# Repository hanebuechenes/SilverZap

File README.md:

## 📜 Lizenzierung / License

Dieses Projekt ist unter dualen Open-Source-Lizenzen veröffentlicht:

* **Hardware & Design (KiCad, Gerber, 3D-STL/STEP):**  
  Lizenziert unter [Creative Commons Attribution 4.0 International (CC BY 4.0)](LICENSE-HARDWARE.txt).  

* **Software & Firmware (C++ Source Code):**  
  Lizenziert unter der [GNU General Public License v3.0 (GPLv3)](LICENSE).

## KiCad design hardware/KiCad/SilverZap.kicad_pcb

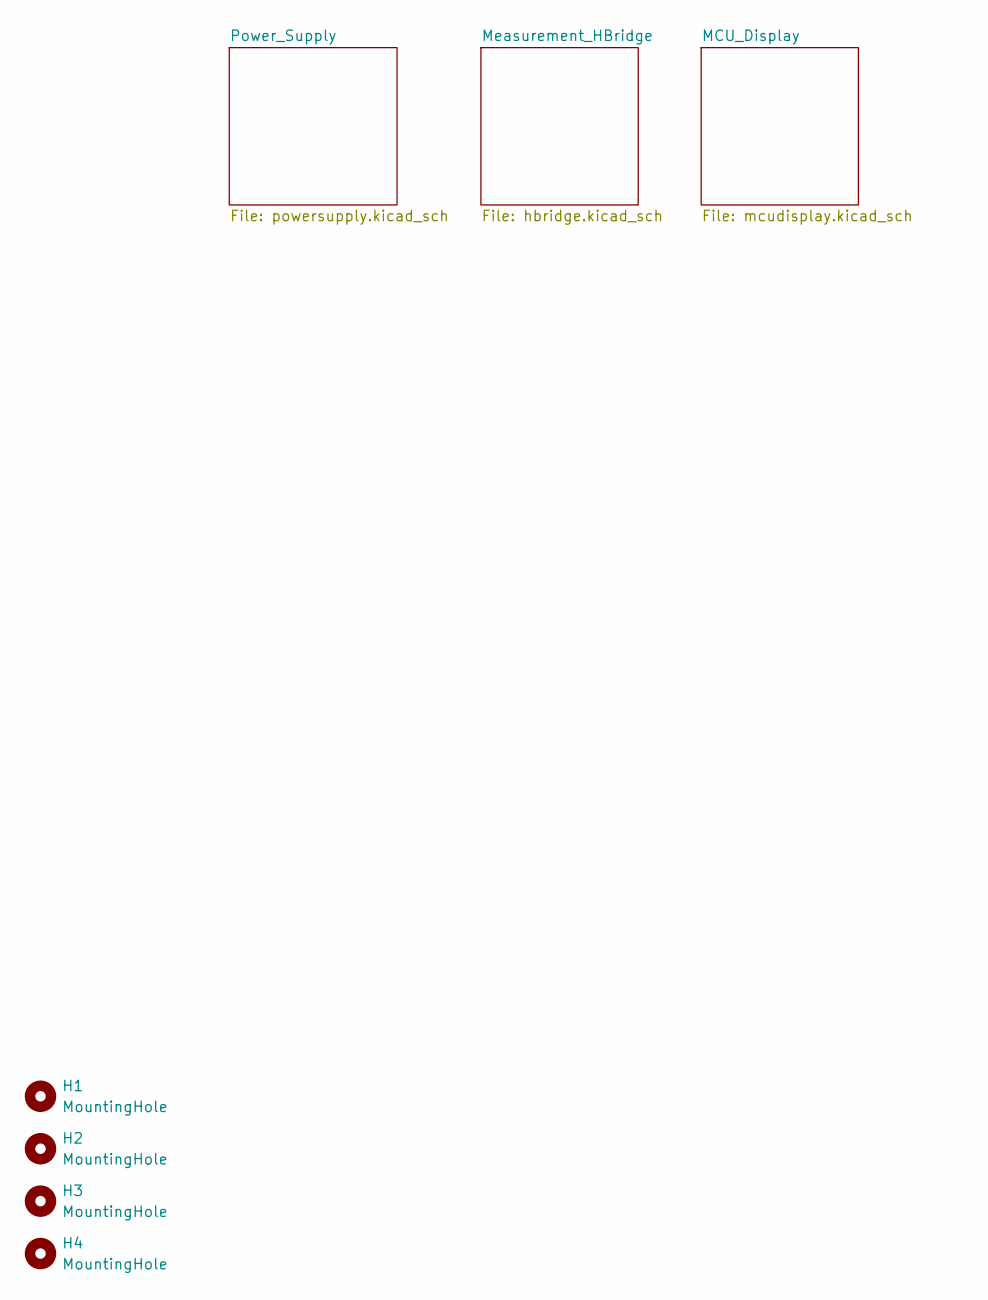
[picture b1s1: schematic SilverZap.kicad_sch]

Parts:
H1, H2, H3, H4: MountingHole; MountingHole_3.2mm_M3

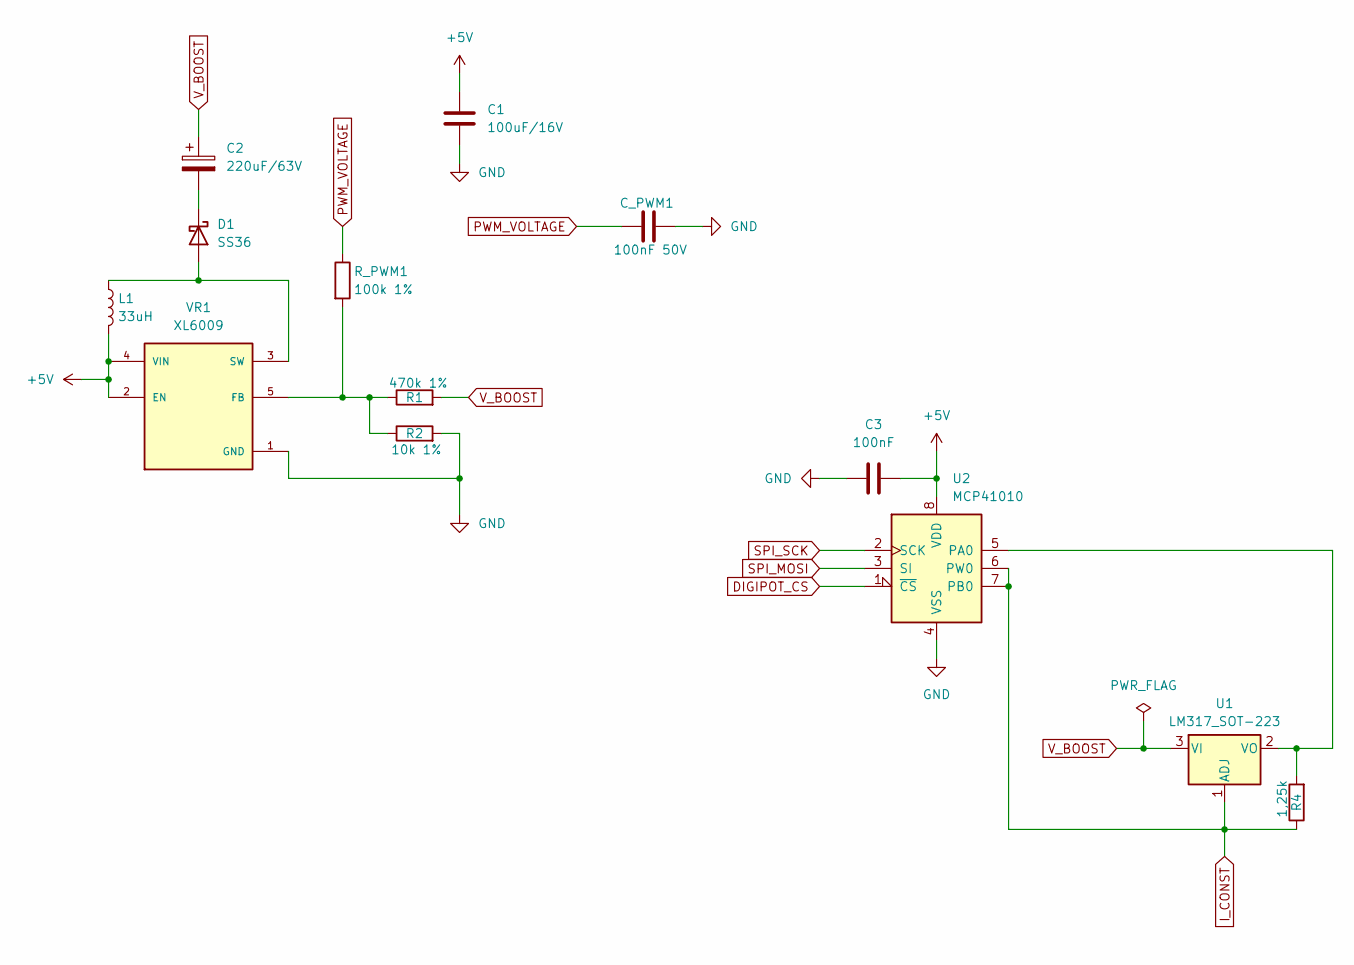
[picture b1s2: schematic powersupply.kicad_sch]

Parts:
C1: 100uF/16V; C_1206_3216Metric
C2: 220uF/63V; CP_Radial_D10.0mm_P5.00mm
C3: 100nF; C_0805_2012Metric
C_PWM1: 100nF 50V; R_0805_2012Metric
D1: SS36; D_SMB
L1: 33uH; L_12x12mm_H6mm
R1: 470k 1%; R_0805_2012Metric
R2: 10k 1%; R_0805_2012Metric
R4: 1,25k; R_0805_2012Metric
R_PWM1: 100k 1%; R_0805_2012Metric
U1: LM317_SOT-223; SOT-223-3_TabPin2
U2: MCP41010; SOIC-8_3.9x4.9mm_P1.27mm
VR1: XL6009; DPAK170P1435X465-6N; PARTREV 1.1

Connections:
+5V: C1.1, C3.2, L1.2, U2.8 (VDD), VR1.2 (EN), VR1.4 (VIN); also elsewhere on the board
DIGIPOT_CS: U2.1 (~CS); also elsewhere on the board
GND: C1.2, C3.1, C_PWM1.2, R2.2, U2.4 (VSS), VR1.1 (GND); also elsewhere on the board
I_CONST: R4.1, U1.1 (ADJ), U2.6 (PW0), U2.7 (PB0); also elsewhere on the board
unnamed: D1.2 (A), L1.1, VR1.3 (SW), VR1.6 (SW)
unnamed: C2.2, D1.1 (K)
unnamed: R4.2, U1.2 (VO), U2.5 (PA0)
unnamed: R1.1, R2.1, R_PWM1.2, VR1.5 (FB)
PWM_VOLTAGE: C_PWM1.1, R_PWM1.1; also elsewhere on the board
SPI_MOSI: U2.3 (SI); also elsewhere on the board
SPI_SCK: U2.2 (SCK); also elsewhere on the board
V_BOOST: C2.1, R1.2, U1.3 (VI)

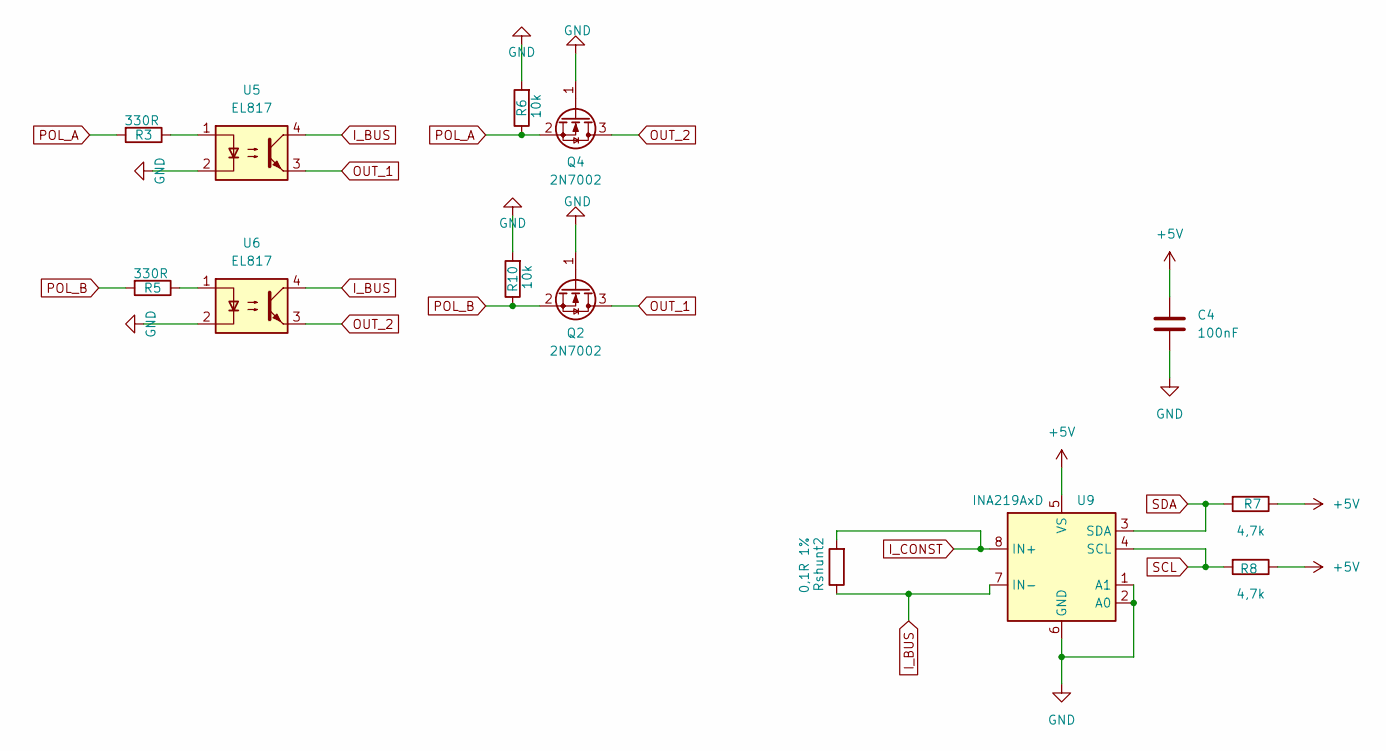
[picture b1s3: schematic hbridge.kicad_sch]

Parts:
C4: 100nF; C_0805_2012Metric
Q2, Q4: 2N7002; SOT-23
R3, R5: 330R; R_0805_2012Metric
R6, R10: 10k; R_0805_2012Metric
R7, R8: 4,7k; R_0805_2012Metric
Rshunt2: 0,1R 1%; R_1206_3216Metric
U5, U6: EL817; DIP-4_W7.62mm
U9: INA219AxD; SOIC-8_3.9x4.9mm_P1.27mm

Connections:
+5V: C4.1, R7.1, R8.1, U9.5 (VS); also elsewhere on the board
GND: C4.2, Q2.1 (G), Q4.1 (G), R6.2, R10.2, U5.2, U6.2, U9.1 (A1), U9.2 (A0), U9.6 (GND); also elsewhere on the board
I_BUS: Rshunt2.1, U5.4, U6.4, U9.7 (IN-)
I_CONST: Rshunt2.2, U9.8 (IN+); also elsewhere on the board
unnamed: R3.1, U5.1
unnamed: R5.1, U6.1
OUT_1: Q2.3 (D), U5.3; also elsewhere on the board
OUT_2: Q4.3 (D), U6.3; also elsewhere on the board
POL_A: Q4.2 (S), R3.2, R6.1; also elsewhere on the board
POL_B: Q2.2 (S), R5.2, R10.1; also elsewhere on the board
SCL: R8.2, U9.4 (SCL); also elsewhere on the board
SDA: R7.2, U9.3 (SDA); also elsewhere on the board

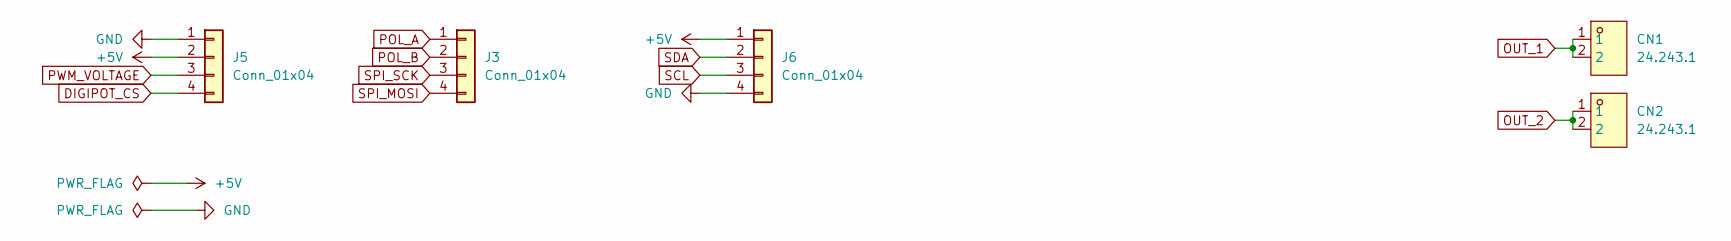
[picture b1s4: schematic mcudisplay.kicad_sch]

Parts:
CN1, CN2: 24.243.1; CONN-TH_24.243.1_RED; MPN 24.243.1; LCSC Part C7437321
J3, J5, J6: Conn_01x04; JST_PH_B4B-PH-K_1x04_P2.00mm_Vertical

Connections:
+5V: J5.2, J6.1; also elsewhere on the board
DIGIPOT_CS: J5.4; also elsewhere on the board
GND: J5.1, J6.4; also elsewhere on the board
OUT_1: CN1.1, CN1.2; also elsewhere on the board
OUT_2: CN2.1, CN2.2; also elsewhere on the board
POL_A: J3.1; also elsewhere on the board
POL_B: J3.2; also elsewhere on the board
PWM_VOLTAGE: J5.3; also elsewhere on the board
SCL: J6.3; also elsewhere on the board
SDA: J6.2; also elsewhere on the board
SPI_MOSI: J3.4; also elsewhere on the board
SPI_SCK: J3.3; also elsewhere on the board

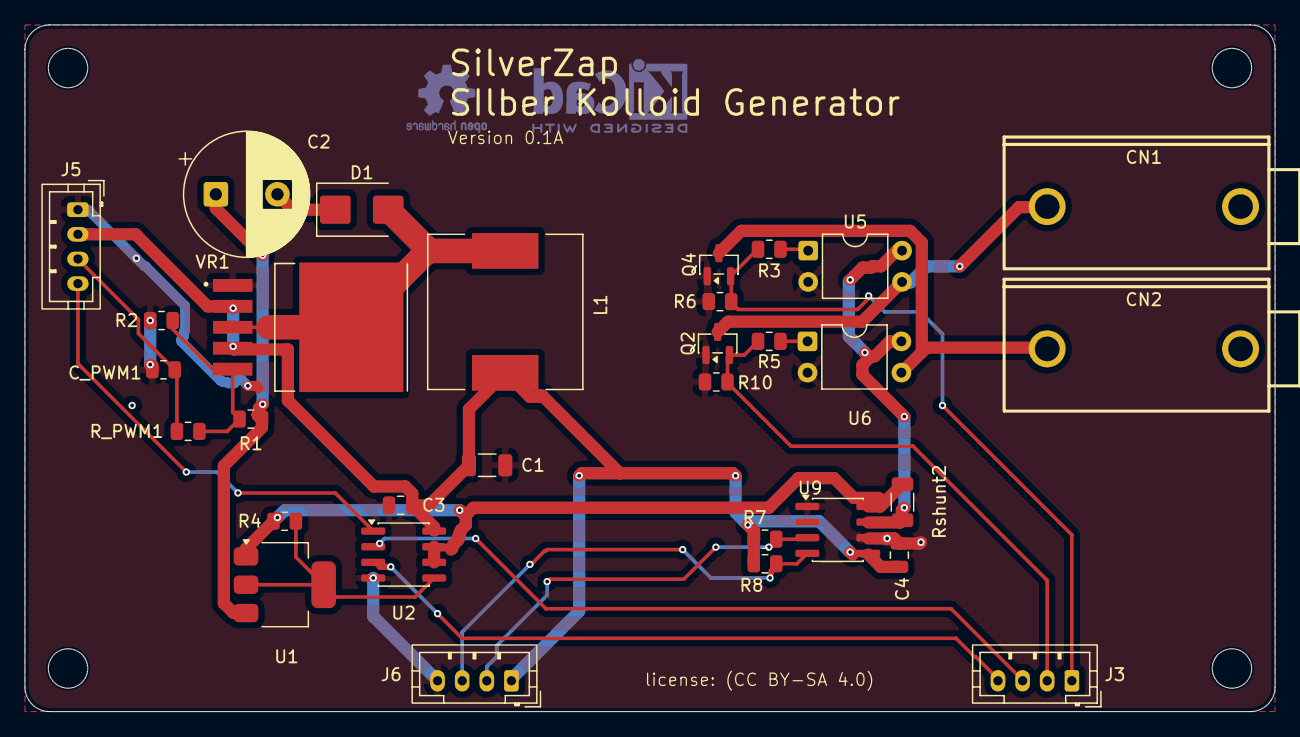
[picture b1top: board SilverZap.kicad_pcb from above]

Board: 2 copper layers, 101.5 x 55.8 mm, 35 parts (0 on the bottom side), 21 nets.

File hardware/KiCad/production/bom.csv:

Designator,Footprint,Quantity,Value,LCSC Part #
C1,1206,1,100uF/16V,
C2,CP_Radial_D10.0mm_P5.00mm,1,220uF/63V,
"C3, C4",0805,2,100nF,
"CN1, CN2",CONN-TH_24.243.1_RED,2,24.243.1,C7437321
C_PWM1,0805,1,100nF 50V,
D1,D_SMB,1,SS36,
"J3, J5, J6",JST_PH_B4B-PH-K_1x04_P2.00mm_Vertical,3,Conn_01x04,
L1,L_12x12mm_H6mm,1,33uH,
"Q2, Q4",SOT-23,2,2N7002,
R1,0805,1,470k 1%,
"R10, R6",0805,2,10k,
R2,0805,1,10k 1%,
"R3, R5",0805,2,330R,
R4,0805,1,"1,25k",
"R7, R8",0805,2,"4,7k",
RSHUNT2,1206,1,"0,1R 1%",
R_PWM1,0805,1,100k 1%,
U1,SOT-223-3_TabPin2,1,LM317_SOT-223,
U2,SOIC-8_3.9x4.9mm_P1.27mm,1,MCP41010,
"U5, U6",DIP-4_W7.62mm,2,EL817,
U9,SOIC-8_3.9x4.9mm_P1.27mm,1,INA219AxD,
VR1,DPAK170P1435X465-6N,1,XL6009,

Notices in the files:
hardware/KiCad/SilverZap.kicad_pcb:
license: (CC BY-SA 4.0)
